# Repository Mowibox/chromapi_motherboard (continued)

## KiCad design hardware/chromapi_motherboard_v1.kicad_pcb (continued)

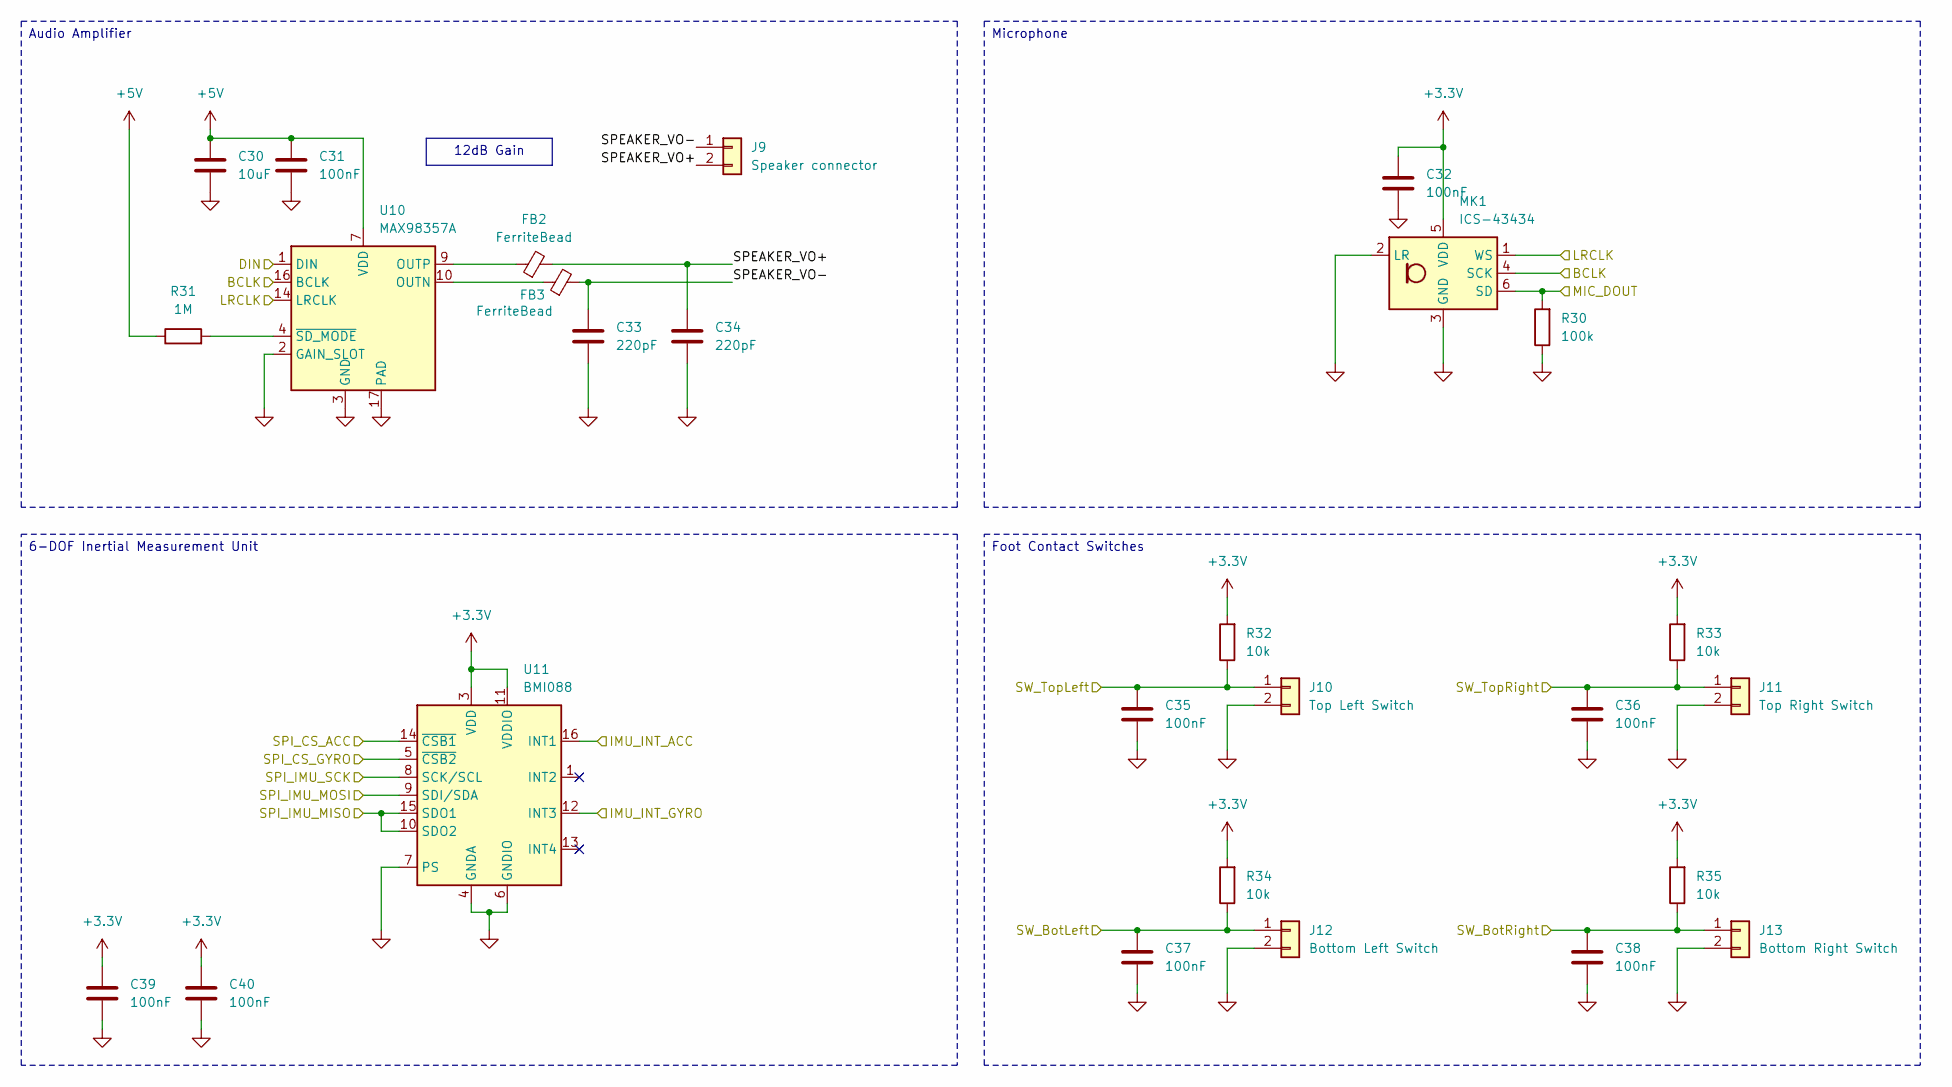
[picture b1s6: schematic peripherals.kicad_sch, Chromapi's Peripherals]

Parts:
C30: 10uF; C_0805_2012Metric; MPN CL21A106KAYNNNE; JLCPCB Part # C15850
C31, C32, C35, C36, C37, C38, C39, C40: 100nF; C_0603_1608Metric; MPN CC0603KRX7R9BB104; JLCPCB Part # C14663
C33, C34: 220pF; C_0603_1608Metric; MPN CL10B221KB8NNNC; JLCPCB Part # C1603
FB2, FB3: FerriteBead; L_0805_2012Metric; MPN MPZ2012S331AT000; JLCPCB Part # C76819
J9: Speaker connector; JST_PH_S2B-PH-K_1x02_P2.00mm_Horizontal; MPN S2B-PH-K-S(LF)(SN); JLCPCB Part # C173752
J10: Top Left Switch; JST_XH_B2B-XH-A_1x02_P2.50mm_Vertical; MPN B2B-XH-A(LF)(SN); JLCPCB Part # C158012
J11: Top Right Switch; JST_XH_B2B-XH-A_1x02_P2.50mm_Vertical; MPN B2B-XH-A(LF)(SN); JLCPCB Part # C158012
J12: Bottom Left Switch; JST_XH_B2B-XH-A_1x02_P2.50mm_Vertical; MPN B2B-XH-A(LF)(SN); JLCPCB Part # C158012
J13: Bottom Right Switch; JST_XH_B2B-XH-A_1x02_P2.50mm_Vertical; MPN B2B-XH-A(LF)(SN); JLCPCB Part # C158012
MK1: ICS-43434; InvenSense_ICS-43434-6_3.5x2.65mm; MPN ICS-43434; JLCPCB Part # C5656610
R30: 100k; R_0603_1608Metric; MPN 0603WAF1003T5E; JLCPCB Part # C25803
R31: 1M; R_0402_1005Metric; MPN 0402WGF1004TCE; JLCPCB Part # C26083
R32, R33, R34, R35: 10k; R_0402_1005Metric; MPN 0402WGF1002TCE; JLCPCB Part # C25744
U10: MAX98357A; TQFN-16-1EP_3x3mm_P0.5mm_EP1.23x1.23mm; MPN MAX98357AETE+T; JLCPCB Part # C910544
U11: BMI088; Bosch_LGA-16_4.5x3mm_P0.5mm_LayoutBorder7x1y_ClockwisePinNu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; MPN BMI088; JLCPCB Part # C194919

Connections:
+3.3V: C32.1, C39.1, C40.1, MK1.5 (VDD), R32.2, R33.2, R34.2, R35.2, U11.3 (VDD), U11.11 (VDDIO); also elsewhere on the board
+5V: C30.1, C31.1, R31.1, U10.7 (VDD), U10.8 (VDD); also elsewhere on the board
/Peripherals (Sensors & Audio)/BCLK: MK1.4 (SCK), U10.16 (BCLK); also elsewhere on the board
/Peripherals (Sensors & Audio)/DIN: U10.1 (DIN); also elsewhere on the board
/Peripherals (Sensors & Audio)/IMU_INT_ACC: U11.16 (INT1); also elsewhere on the board
/Peripherals (Sensors & Audio)/IMU_INT_GYRO: U11.12 (INT3); also elsewhere on the board
/Peripherals (Sensors & Audio)/LRCLK: MK1.1 (WS), U10.14 (LRCLK); also elsewhere on the board
/Peripherals (Sensors & Audio)/MIC_DOUT: MK1.6 (SD), R30.2; also elsewhere on the board
/Peripherals (Sensors & Audio)/SPEAKER_VO+: C34.1, FB2.2, J9.2
/Peripherals (Sensors & Audio)/SPEAKER_VO-: C33.1, FB3.2, J9.1
/Peripherals (Sensors & Audio)/SPI_CS_ACC: U11.14 (~CSB1); also elsewhere on the board
/Peripherals (Sensors & Audio)/SPI_CS_GYRO: U11.5 (~CSB2); also elsewhere on the board
/Peripherals (Sensors & Audio)/SPI_IMU_MISO: U11.10 (SDO2), U11.15 (SDO1); also elsewhere on the board
/Peripherals (Sensors & Audio)/SPI_IMU_MOSI: U11.9 (SDI/SDA); also elsewhere on the board
/Peripherals (Sensors & Audio)/SPI_IMU_SCK: U11.8 (SCK/SCL); also elsewhere on the board
/Peripherals (Sensors & Audio)/SW_BotLeft: C37.1, J12.1, R34.1; also elsewhere on the board
/Peripherals (Sensors & Audio)/SW_BotRight: C38.1, J13.1, R35.1; also elsewhere on the board
/Peripherals (Sensors & Audio)/SW_TopLeft: C35.1, J10.1, R32.1; also elsewhere on the board
/Peripherals (Sensors & Audio)/SW_TopRight: C36.1, J11.1, R33.1; also elsewhere on the board
GND: C30.2, C31.2, C32.2, C33.2, C34.2, C35.2, C36.2, C37.2, C38.2, C39.2, C40.2, J10.2, J11.2, J12.2, J13.2, MK1.2 (LR), MK1.3 (GND), R30.1, U10.2 (GAIN_SLOT), U10.3 (GND), U10.11 (GND), U10.15 (GND), U10.17 (PAD), U11.2 (GNDA), U11.4 (GNDA), U11.6 (GNDIO), U11.7 (PS); also elsewhere on the board
unnamed: FB3.1, U10.10 (OUTN)
unnamed: FB2.1, U10.9 (OUTP)
unnamed: R31.2, U10.4 (~SD_MODE)

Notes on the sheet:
12dB Gain
Audio Amplifier
6-DOF Inertial Measurement Unit
Microphone
Foot Contact Switches

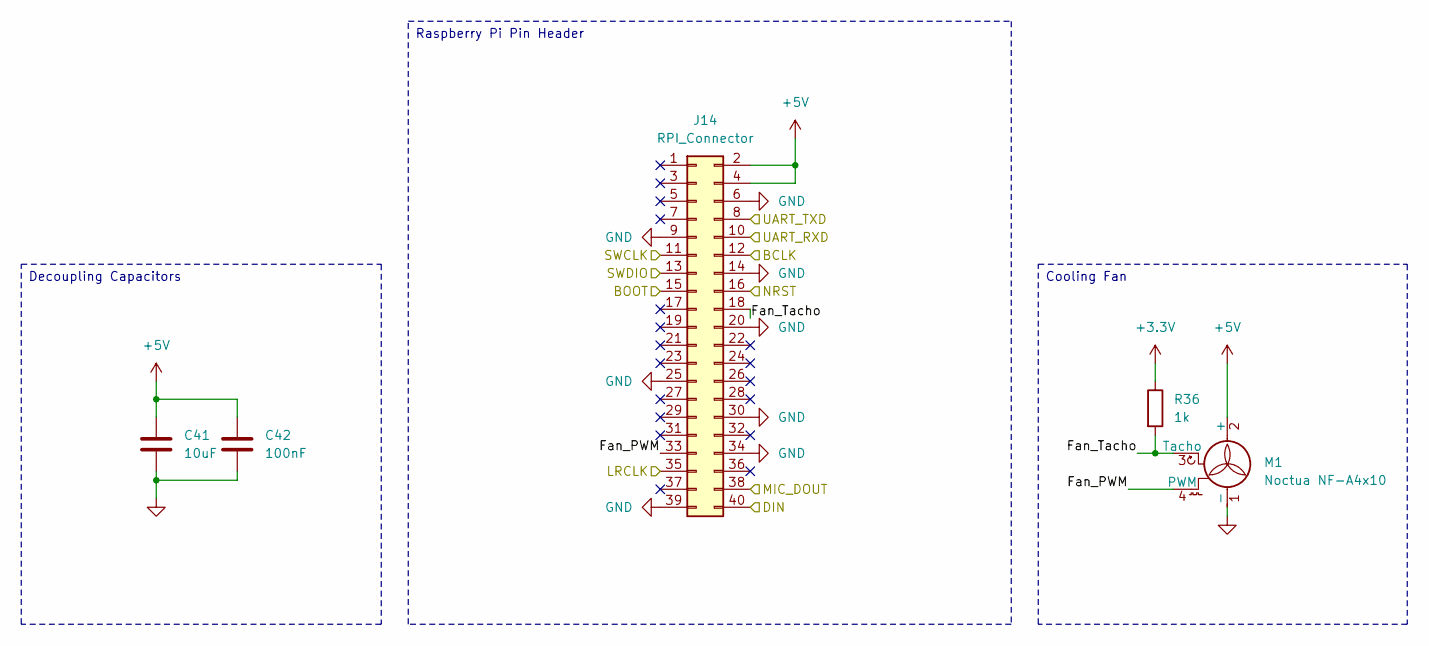
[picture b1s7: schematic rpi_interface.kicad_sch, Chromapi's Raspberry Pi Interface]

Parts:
C41: 10uF; C_0805_2012Metric; MPN CL21A106KAYNNNE; JLCPCB Part # C15850
C42: 100nF; C_0402_1005Metric; MPN CL05B104KB54PNC; JLCPCB Part # C307331
J14: RPI_Connector; PinSocket_2x20_P2.54mm_Vertical; MPN ESQ-120-13-G-D
M1: Noctua NF-A4x10; FanPinHeader_1x04_P2.54mm_Vertical; MPN 47053-1000; JLCPCB Part # C240840
R36: 1k; R_0603_1608Metric; MPN 0603WAF1001T5E; JLCPCB Part # C21190

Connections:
+3.3V: R36.1; also elsewhere on the board
+5V: C41.1, C42.1, J14.2, J14.4, M1.2 (+); also elsewhere on the board
/Peripherals (Sensors & Audio)/BCLK: J14.12; also elsewhere on the board
/Peripherals (Sensors & Audio)/DIN: J14.40; also elsewhere on the board
/Peripherals (Sensors & Audio)/LRCLK: J14.35; also elsewhere on the board
/Peripherals (Sensors & Audio)/MIC_DOUT: J14.38; also elsewhere on the board
/Raspberry Pi Interface/BOOT: J14.15; also elsewhere on the board
/Raspberry Pi Interface/Fan_PWM: J14.33, M1.4 (PWM)
/Raspberry Pi Interface/Fan_Tacho: J14.18, M1.3 (Tacho), R36.2
/Raspberry Pi Interface/NRST: J14.16; also elsewhere on the board
/Raspberry Pi Interface/SWCLK: J14.11; also elsewhere on the board
/Raspberry Pi Interface/SWDIO: J14.13; also elsewhere on the board
/Raspberry Pi Interface/UART_RXD: J14.10; also elsewhere on the board
/Raspberry Pi Interface/UART_TXD: J14.8; also elsewhere on the board
GND: C41.2, C42.2, J14.6, J14.9, J14.14, J14.20, J14.25, J14.30, J14.34, J14.39, M1.1 (-); also elsewhere on the board

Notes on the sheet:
Cooling Fan
Decoupling Capacitors
Raspberry Pi Pin Header

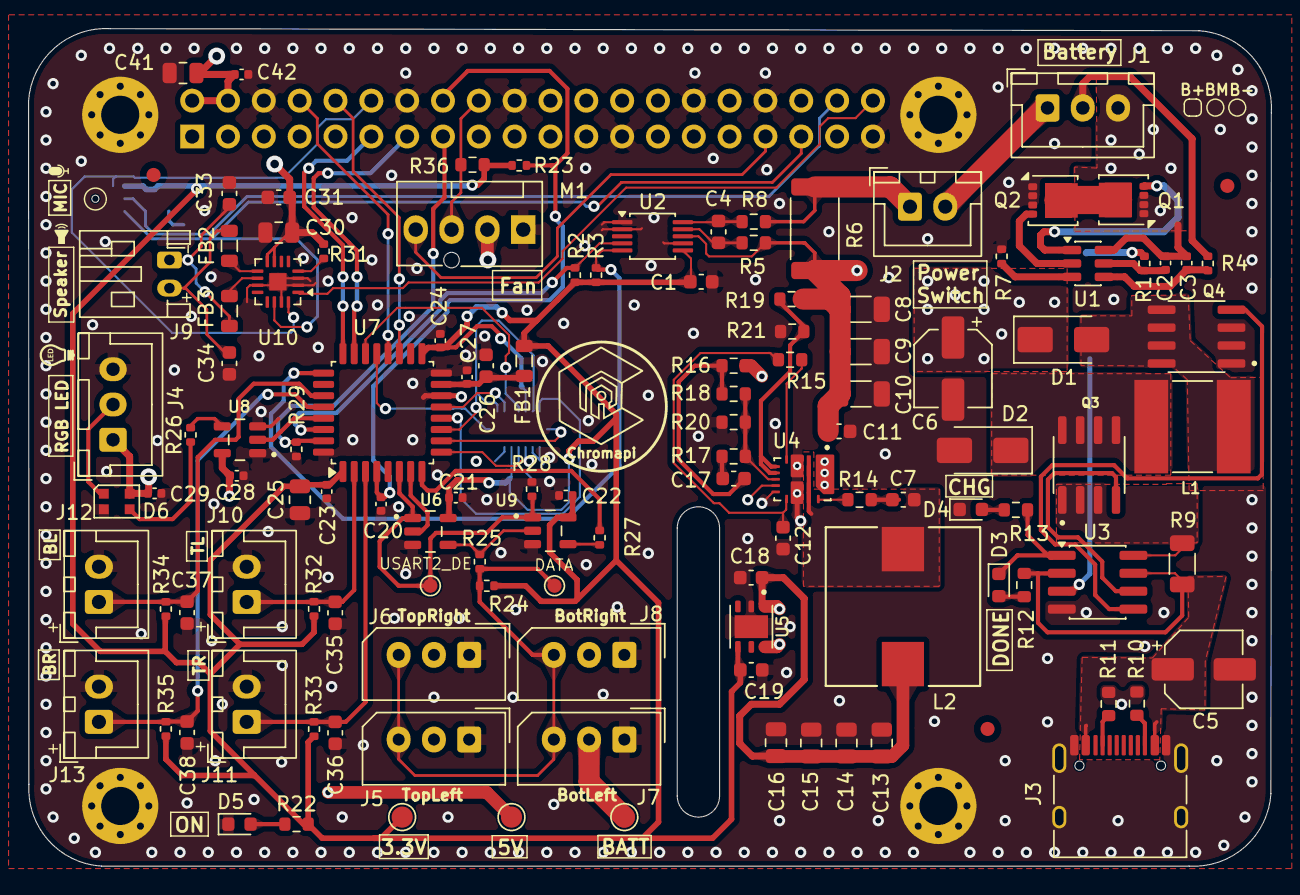
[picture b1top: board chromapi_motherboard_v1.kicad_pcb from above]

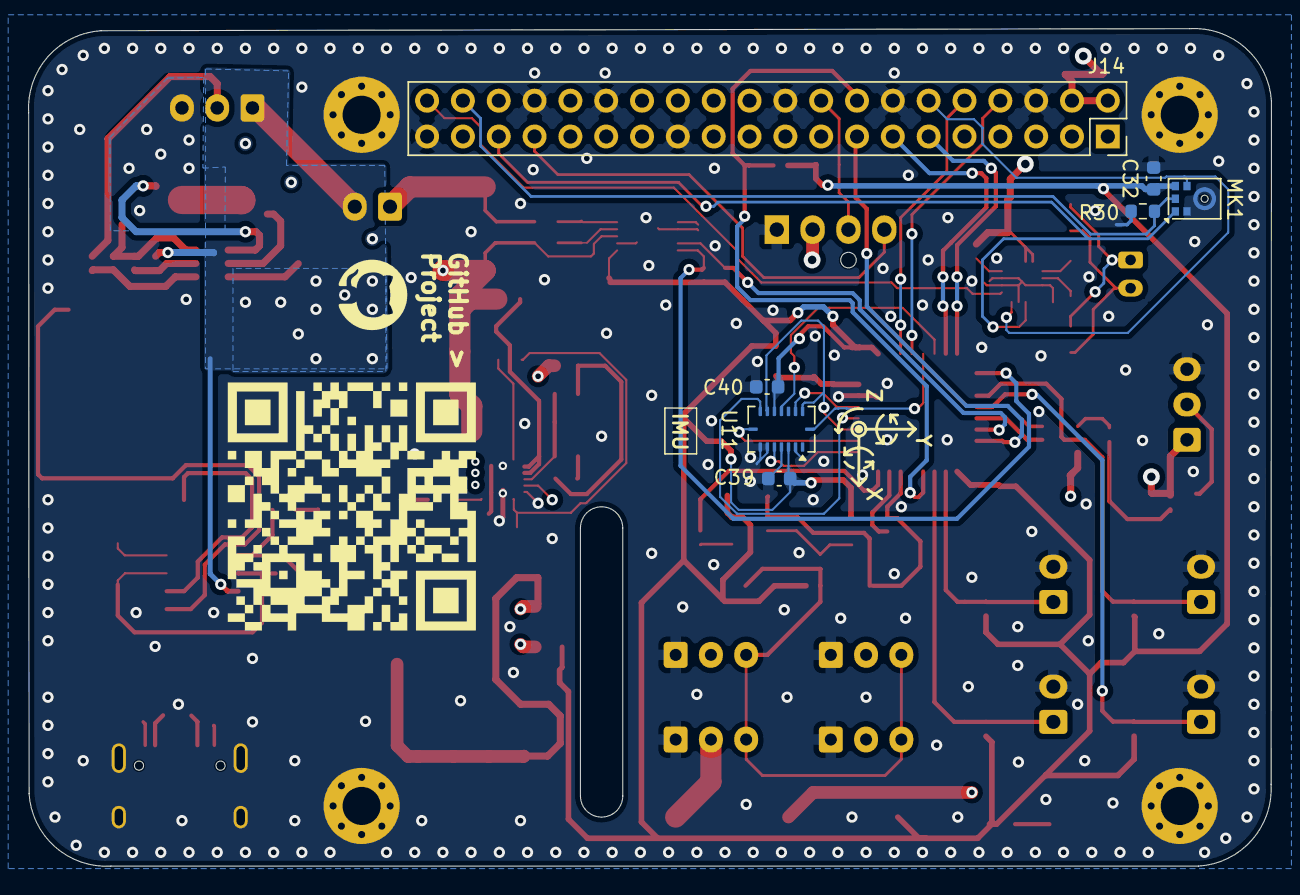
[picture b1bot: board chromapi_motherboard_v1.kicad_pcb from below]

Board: 4 copper layers, 88.1 x 59.4 mm, 133 parts (7 on the bottom side), 78 nets.

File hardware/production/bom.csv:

Designator,Footprint,Quantity,Value,LCSC Part #
"C1, C11, C31, C32, C35, C36, C37, C38, C39, C4, C40, C7",0603,12,100nF,C14663
"C10, C8, C9",1206,3,22uF,C12891
C12,0603,1,2.2uF,C23630
"C13, C14, C15, C16",0805,4,22uF,C45783
C17,0603,1,470pF,C106211
"C18, C19, C26",0603,3,1uF,C15849
"C2, C20, C21, C22, C23, C24, C27, C28, C29, C3, C42",0402,11,100nF,C307331
"C25, C30, C41",0805,3,10uF,C15850
"C33, C34",0603,2,220pF,C1603
"C5, C6",CP_Elec_5x5.8,2,22uF,C336501
"D1, D2",D_SMA,2,SS34,C8678
D3,0603,1,DONE_LED,C12624
D4,0603,1,CHG_LED,C2286
D5,0603,1,ON_LED,C2288
D6,LED_WS2812B-2020_PLCC4_2.0x2.0mm,1,WS2812B,C965555
"FB1, FB2, FB3",0805,3,FerriteBead,C76819
J1,JST_XH_B3B-XH-A_1x03_P2.50mm_Vertical,1,Battery Input,C144394
J10,JST_XH_B2B-XH-A_1x02_P2.50mm_Vertical,1,Top Left Switch,C158012
J11,JST_XH_B2B-XH-A_1x02_P2.50mm_Vertical,1,Top Right Switch,C158012
J12,JST_XH_B2B-XH-A_1x02_P2.50mm_Vertical,1,Bottom Left Switch,C158012
J13,JST_XH_B2B-XH-A_1x02_P2.50mm_Vertical,1,Bottom Right Switch,C158012
J14,PinSocket_2x20_P2.54mm_Vertical,1,RPI_Connector,ESQ-120-13-G-D
J2,JST_XH_B2B-XH-A_1x02_P2.50mm_Vertical,1,Power Switch,C158012
J3,USB_C_Receptacle_HRO_TYPE-C-31-M-12,1,USB_C_Receptacle_USB2.0_14P,C165948
J4,JST_XH_B3B-XH-A_1x03_P2.50mm_Vertical,1,RGB LED Ring,C144394
J5,Molex_SPOX_5267-03A_1x03_P2.50mm_Vertical,1,Conn_TopLeft,5267-03A
J6,Molex_SPOX_5267-03A_1x03_P2.50mm_Vertical,1,Conn_TopRight,5267-03A
J7,Molex_SPOX_5267-03A_1x03_P2.50mm_Vertical,1,Conn_BotLeft,5267-03A
J8,Molex_SPOX_5267-03A_1x03_P2.50mm_Vertical,1,Conn_BotRight,5267-03A
J9,JST_PH_S2B-PH-K_1x02_P2.00mm_Horizontal,1,Speaker connector,C173752
L1,INDM6864X300N,1,4.7uH,C553961
L2,IND_1040-WE-HCI_WRE,1,1.5uH,C5914133
M1,FanPinHeader_1x04_P2.54mm_Vertical,1,Noctua NF-A4x10,C240840
MK1,InvenSense_ICS-43434-6_3.5x2.65mm,1,ICS-43434,C5656610
"Q1, Q2",VSON-8_3.3x3.3mm_P0.65mm_NexFET,2,CSD17581Q3A,C2861705
Q3,ao4435_SOIC127P600X175-8N,1,AO4435,C2944310
Q4,ao4435_SOIC127P600X175-8N,1,AO4468,C87410
"R1, R26, R4",0402,3,330,C25104
"R10, R11",0603,2,5.1k,C23186
"R12, R13, R17, R22, R36",0603,5,1k,C21190
"R14, R16, R5, R8",0603,4,0,C21189
"R15, R19",0603,2,100k,C844916
R18,0603,1,137k,C22872
"R2, R23, R24, R28, R29, R3, R32, R33, R34, R35",0402,10,10k,C25744
R20,0603,1,18.2k,C137784
R21,0603,1,68k,C844803
"R25, R27",0402,2,100,C25076
R30,0603,1,100k,C25803
R31,0402,1,1M,C26083
R6,2512,1,2m,C5375414
R7,0402,1,2k,C4109
R9,1206,1,60m,C728501
U1,SOT-23-6,1,HY2120,C116509
U10,TQFN-16-1EP_3x3mm_P0.5mm_EP1.23x1.23mm,1,MAX98357A,C910544
U11,Bosch_LGA-16_4.5x3mm_P0.5mm_LayoutBorder7x1y_ClockwisePinNumbering,1,BMI088,C194919
U2,TSSOP-10_3x3mm_P0.5mm,1,INA226,C2653835
U3,SOP-8_3.76x4.96mm_P1.27mm,1,CN3302,C559039
U4,TPS513885VABR,1,TPS51388VABR,C41935536
U5,ld39050PU33R_SON95P300X300X100-7N,1,LD39050PU33R,C132827
U6,SOT95P280X145-5N,1,SN74LVC1G126DBVR,C7834
U7,LQFP-32_7x7mm_P0.8mm,1,STM32G431KBTx,C529357
U8,SOT95P280X145-5N,1,SN74AHCT1G125DBVR,C7484
U9,SOT95P280X145-5N,1,SN74LVC1G125DBVR,C23654

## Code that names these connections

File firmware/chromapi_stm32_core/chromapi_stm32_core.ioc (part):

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Mcu.Name=STM32G431K(6-8-B)Tx
Mcu.Package=LQFP32
Mcu.UserName=STM32G431KBTx
PA1.Mode=Hardware Flow Control (RS485)
PA1.Signal=USART2_DE
PA10.Mode=Asynchronous
PA10.Signal=USART1_RX
PA11.GPIOParameters=GPIO_Label
PA11.GPIO_Label=IMU_INT_ACC
PA11.Signal=GPXTI11
PA12.GPIOParameters=GPIO_Label
PA12.GPIO_Label=IMU_INT_GYRO
PA12.Signal=GPXTI12
PA13.Mode=Serial_Wire
PA13.Signal=SYS_JTMS-SWDIO
PA14.Mode=Serial_Wire
PA14.Signal=SYS_JTCK-SWCLK
PA15.GPIOParameters=GPIO_Label
PA15.GPIO_Label=I2C_INA_SCL
PA15.Mode=I2C
PA15.Signal=I2C1_SCL
PA2.Mode=Asynchronous
PA2.Signal=USART2_TX
PA3.GPIOParameters=GPIO_PuPd
PA3.GPIO_PuPd=GPIO_PULLUP
PA3.Mode=Asynchronous
PA3.Signal=USART2_RX
PA4.GPIOParameters=PinState,GPIO_Label
PA4.GPIO_Label=SPI_CS_GYRO
PA4.PinState=GPIO_PIN_SET
PA4.Signal=GPIO_Output
PA5.GPIOParameters=GPIO_Speed,GPIO_Label
PA5.GPIO_Label=SPI_IMU_SCK
PA5.GPIO_Speed=GPIO_SPEED_FREQ_HIGH
PA5.Mode=Full_Duplex_Master
PA5.Signal=SPI1_SCK
PA6.GPIOParameters=GPIO_Speed,GPIO_Label
PA6.GPIO_Label=SPI_IMU_MISO
PA6.GPIO_Speed=GPIO_SPEED_FREQ_HIGH
PA6.Mode=Full_Duplex_Master
PA6.Signal=SPI1_MISO
PA7.GPIOParameters=GPIO_Speed,GPIO_Label
PA7.GPIO_Label=SPI_IMU_MOSI
PA7.GPIO_Speed=GPIO_SPEED_FREQ_HIGH
PA7.Mode=Full_Duplex_Master
PA7.Signal=SPI1_MOSI
PA9.Mode=Asynchronous
PA9.Signal=USART1_TX
PB0.GPIOParameters=PinState,GPIO_Label
PB0.GPIO_Label=SPI_CS_ACC
PB0.PinState=GPIO_PIN_SET
PB0.Signal=GPIO_Output
PB4.GPIOParameters=GPIO_PuPd,GPIO_Label
PB4.GPIO_Label=SW_BotLeft
PB4.GPIO_PuPd=GPIO_NOPULL
PB4.Signal=GPIO_Input
PB5.GPIOParameters=GPIO_PuPd,GPIO_Label
PB5.GPIO_Label=SW_BotRight
PB5.GPIO_PuPd=GPIO_NOPULL
PB5.Signal=GPIO_Input
PB6.GPIOParameters=GPIO_Label
PB6.GPIO_Label=RGB_LED
PB6.Signal=S_TIM4_CH1
PB7.GPIOParameters=GPIO_Label
PB7.GPIO_Label=I2C_INA_SDA
PB7.Mode=I2C
PB7.Signal=I2C1_SDA
PF0-OSC_IN.GPIOParameters=GPIO_PuPd,GPIO_Label
PF0-OSC_IN.GPIO_Label=SW_TopLeft
PF0-OSC_IN.GPIO_PuPd=GPIO_NOPULL
PF0-OSC_IN.Signal=GPIO_Input
PF1-OSC_OUT.GPIOParameters=GPIO_PuPd,GPIO_Label
PF1-OSC_OUT.GPIO_Label=SW_TopRight
PF1-OSC_OUT.GPIO_PuPd=GPIO_NOPULL
PF1-OSC_OUT.Signal=GPIO_Input
RCC.HSE_VALUE=8000000
RCC.SYSCLKFreq_VALUE=160000000
RCC.SYSCLKSource=RCC_SYSCLKSOURCE_PLLCLK
board=custom

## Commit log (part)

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2026-02-09 Adding .gitattributes
2026-02-10 adding tps568230 datasheet
2026-02-10 First draft of Voltage regulation
2026-02-10 Adding hierarchical sheets
2026-02-11 First draft of audio amplifier
2026-02-11 Updating audio amplifier
2026-02-12 Adding IMU
2026-02-12 Finishing IMU schematic
2026-02-12 Adding Force Resistive Sensor
2026-02-12 Updating microphone schematic
2026-02-13 Updating peripherals
2026-02-13 Component sizing in voltage regulator
2026-02-13 Updating voltage regulation schematic
2026-02-16 Adding 5V to 3V3 regulator
2026-02-18 Adding BMS
2026-02-18 Adding datasheets
2026-02-18 First draft of rpi interface
2026-02-19 Finishing power supply and charge schematic
2026-02-19 minor fix
2026-02-19 Adding voltage divider to EN
2026-02-19 Adding logo
2026-02-19 Adding LED datasheet
2026-02-19 Adding rpi interface
2026-02-20 Updating gitignore with Cube IDE
2026-02-20 Adding pin assignements to stm32_mcu_core
2026-02-21 Schematic first draft
2026-02-21 Updating firmware pinout
2026-02-21 Annotating schematic
2026-02-21 Adding pwr flags
2026-02-21 minor fixes
2026-02-21 Updating schematic
2026-02-21 Adding test points
2026-02-21 Highlighting power lines
2026-02-21 Annotating components
2026-02-21 Adding descriptions & datasheets
2026-02-21 Adding power LED status
2026-02-22 Adding footprint & symbol folders
2026-02-22 Adding cooling fan
2026-02-23 Adding footprints
2026-02-23 Updating footprints
2026-02-23 Placing components
2026-02-24 Modyfing components footprints
2026-02-28 Replacing AO4406A by PSMN1R5-30YLC
2026-03-05 Component spacing
2026-03-06 updating component placcement
2026-03-06 updating component placement
2026-03-06 adding chromapi logo to library
2026-03-08 adding 3d models
2026-03-08 adding inductor 3d model
2026-03-10 Adding some MPN/MPR
2026-03-11 Applying first corrections from first review
2026-03-12 Schematic servo tranceiver correction
2026-03-15 IMU modification and Power monitor addition
2026-03-15 Updating placement
2026-03-16 Replacing MOSFET for CSD17581Q3A
2026-03-16 Drawing rpi outline & placement update
2026-03-17 Upgrading voltage regulation circuit in schematic
2026-03-17 Running ERC successfully
2026-03-18 Update component placement
2026-03-22 Upgrading KiCad
2026-04-03 rm cached
2026-04-05 First routing draft
2026-04-05 Routing update
2026-04-08 Updating .gitignore
2026-04-08 Finishing first draft of routing
2026-04-08 Solving DRC
2026-04-08 Adding schematic & bom
2026-04-10 Adding external pullup to NRST
2026-04-10 Rerouting USB charge
2026-04-10 Adding image to repo
2026-04-10 Adding gerbers folder
2026-04-10 Updating MPN and part number
2026-04-11 Adding image to schematic
2026-04-12 Fixing DRC
2026-04-13 Minor routing update
2026-04-13 Updating BOM
2026-04-13 Adding MPN to parts
2026-04-15 Replacing components
2026-04-21 Removing history trim
2026-04-29 Adding IMU reference frame for silkscreen
2026-04-29 Adding IMU position
2026-05-06 Logo update on README.md badge
2026-05-08 Configuring ioc for servo communication
2026-05-08 Rewriting header files
2026-05-09 reformatting files
2026-05-10 Adding ina226 library
2026-05-10 Adding sk6812 library
2026-05-11 fixing DMA for sk6812
2026-05-25 adding bridge
2026-05-25 note on audio issue
2026-05-25 adding IMU driver
2026-05-26 speeding up the mcu
2026-05-26 adding ina226 power measurement
2026-05-30 adding todo
2026-05-31 update get power function
2026-06-02 add register management to bridge
2026-06-02 Add todo for speaker connector
2026-06-10 swap contact switches logic
2026-06-15 update todo list
2026-06-18 add todos
2026-06-21 add chromapi_motherboard.step
2026-06-22 add spi todo
2026-06-22 update ioc according to fix spi conf
2026-06-23 fix spi connection mismatch
2026-06-23 [fixed] change the connector footprint for the speaker
2026-06-23 [fix] change the connector footprint for the speaker
